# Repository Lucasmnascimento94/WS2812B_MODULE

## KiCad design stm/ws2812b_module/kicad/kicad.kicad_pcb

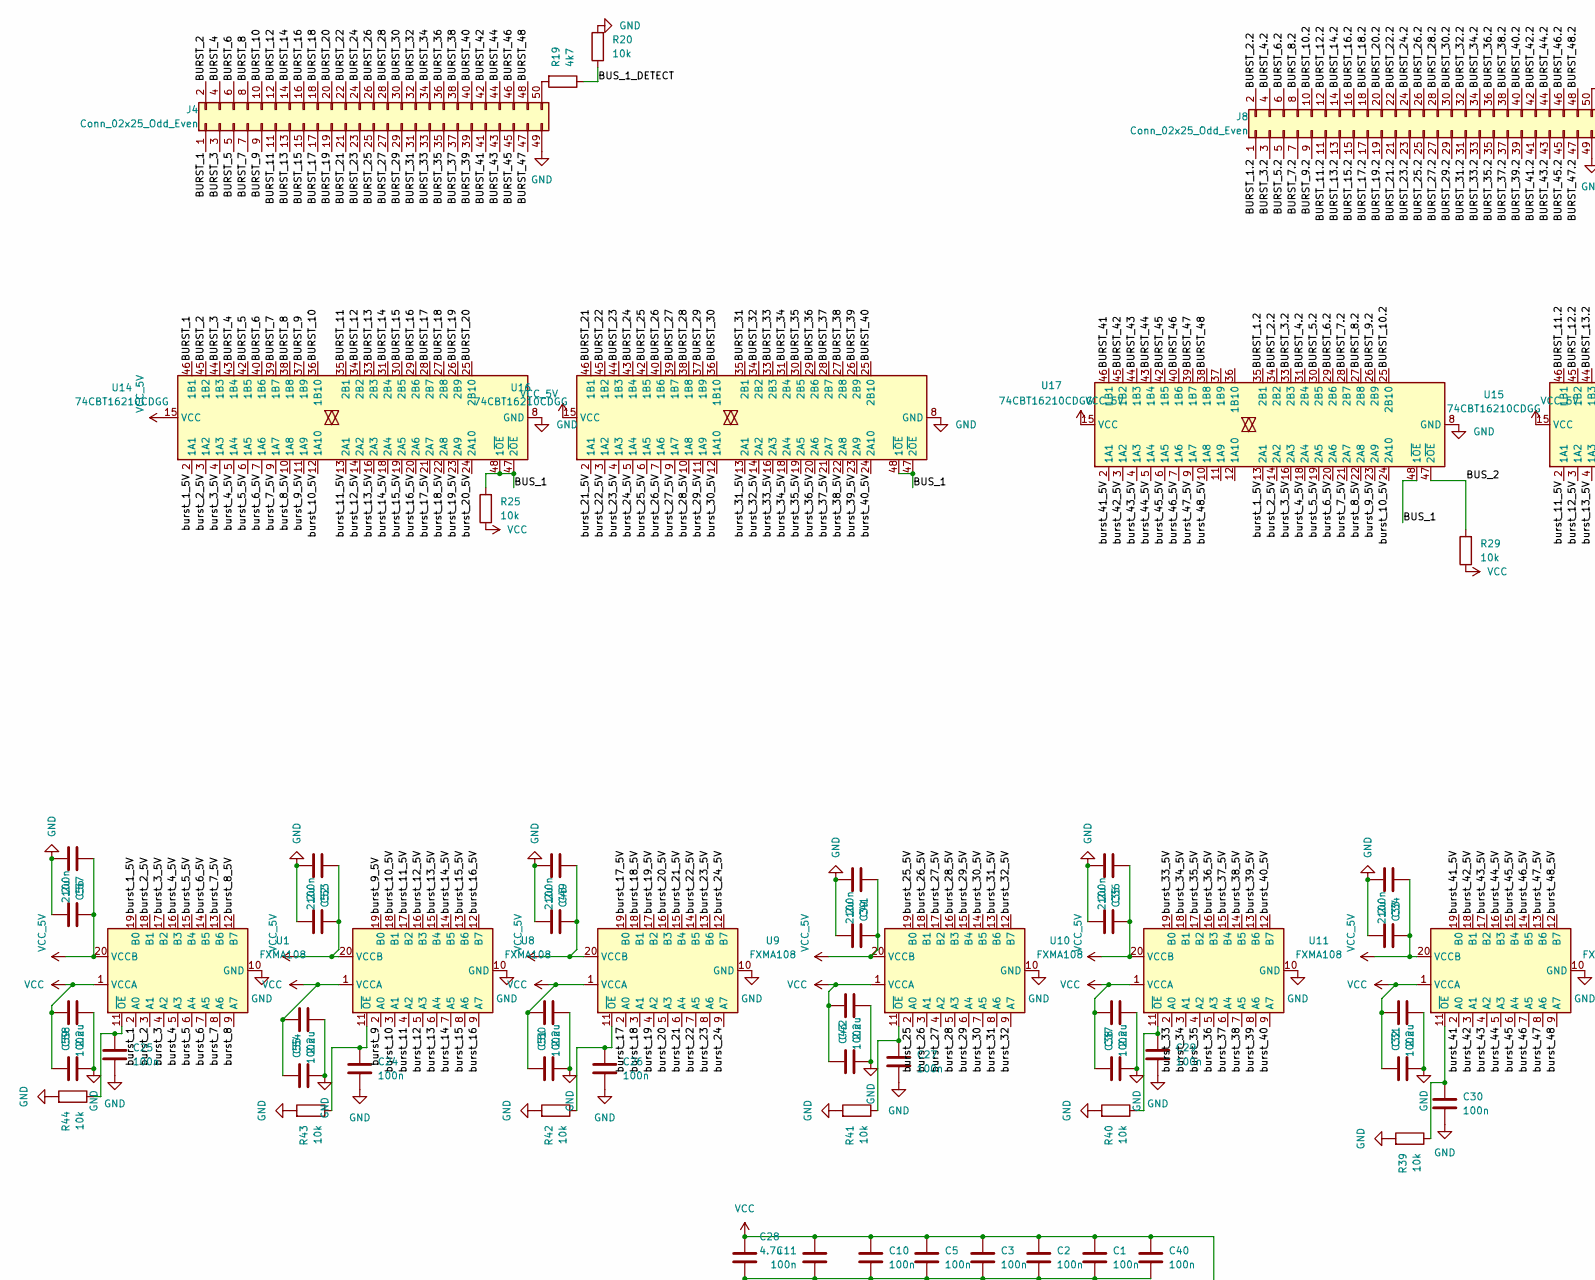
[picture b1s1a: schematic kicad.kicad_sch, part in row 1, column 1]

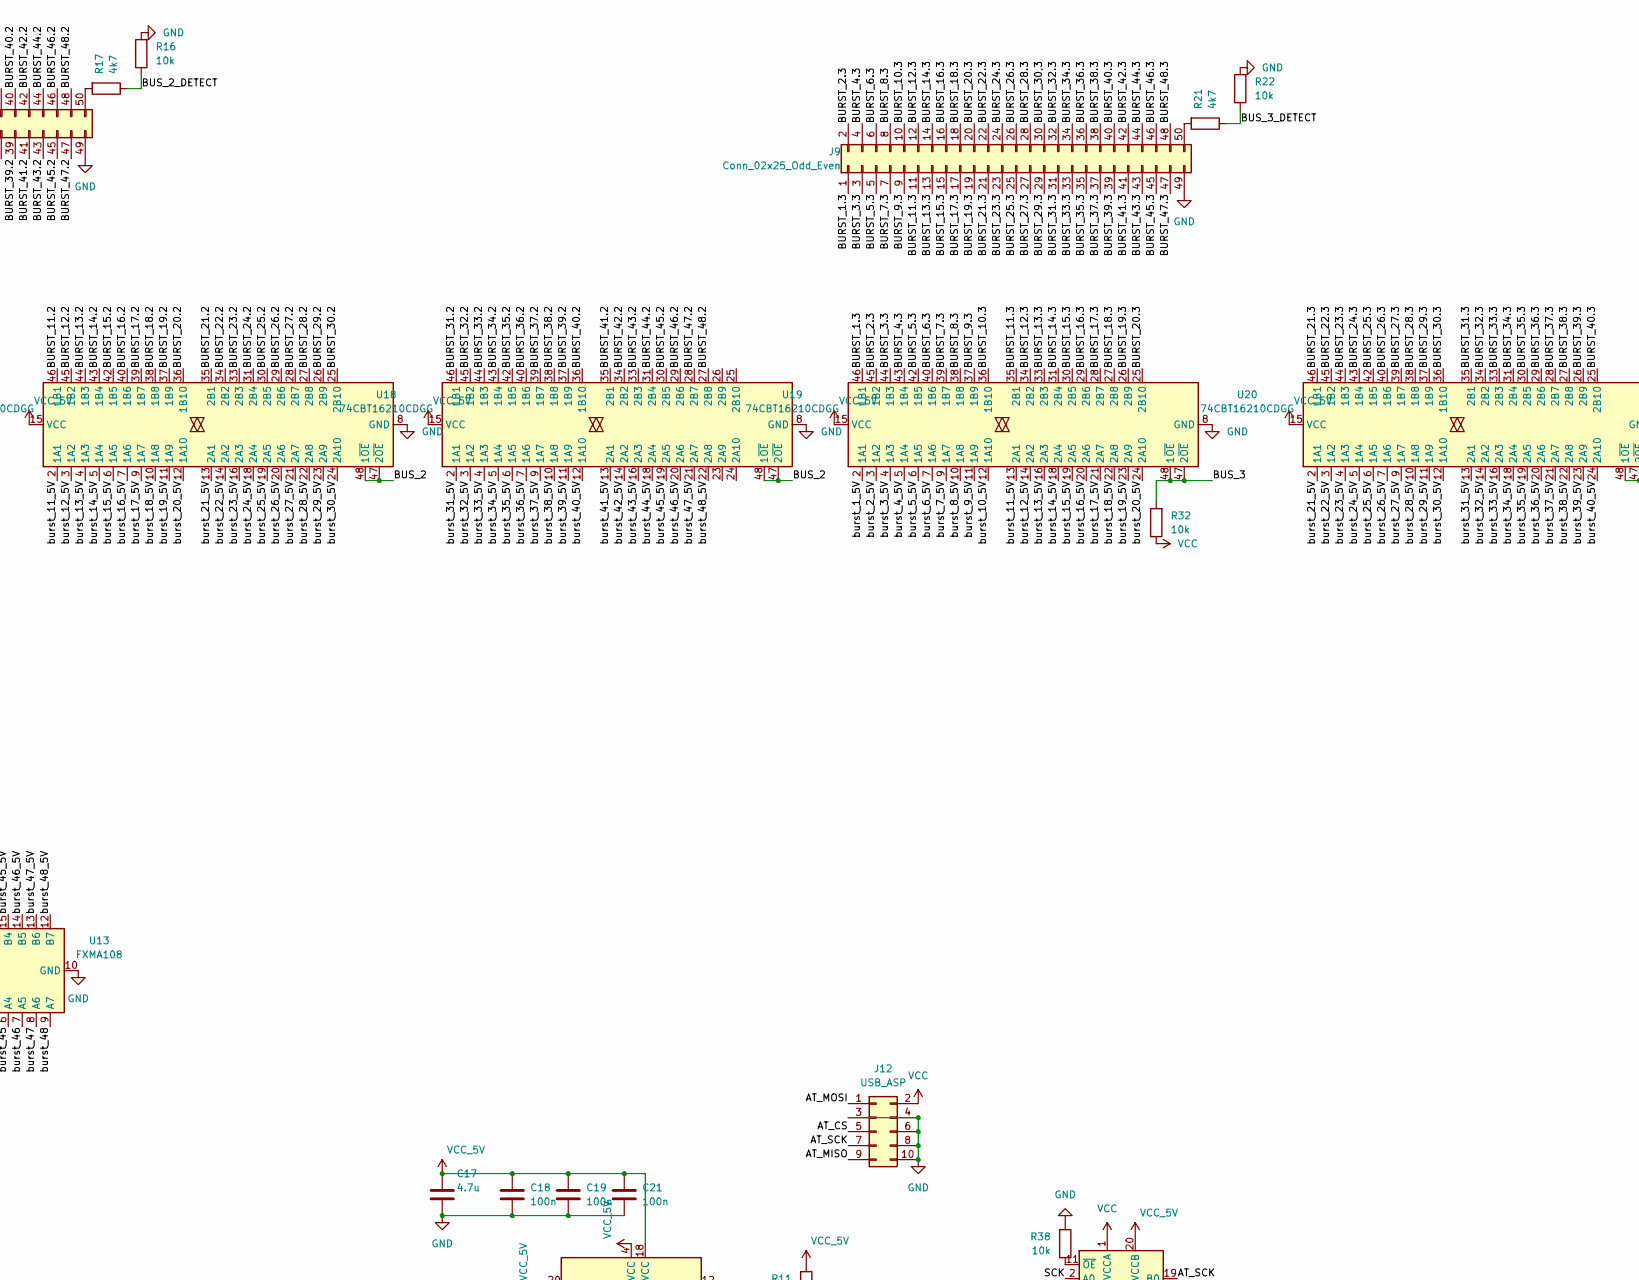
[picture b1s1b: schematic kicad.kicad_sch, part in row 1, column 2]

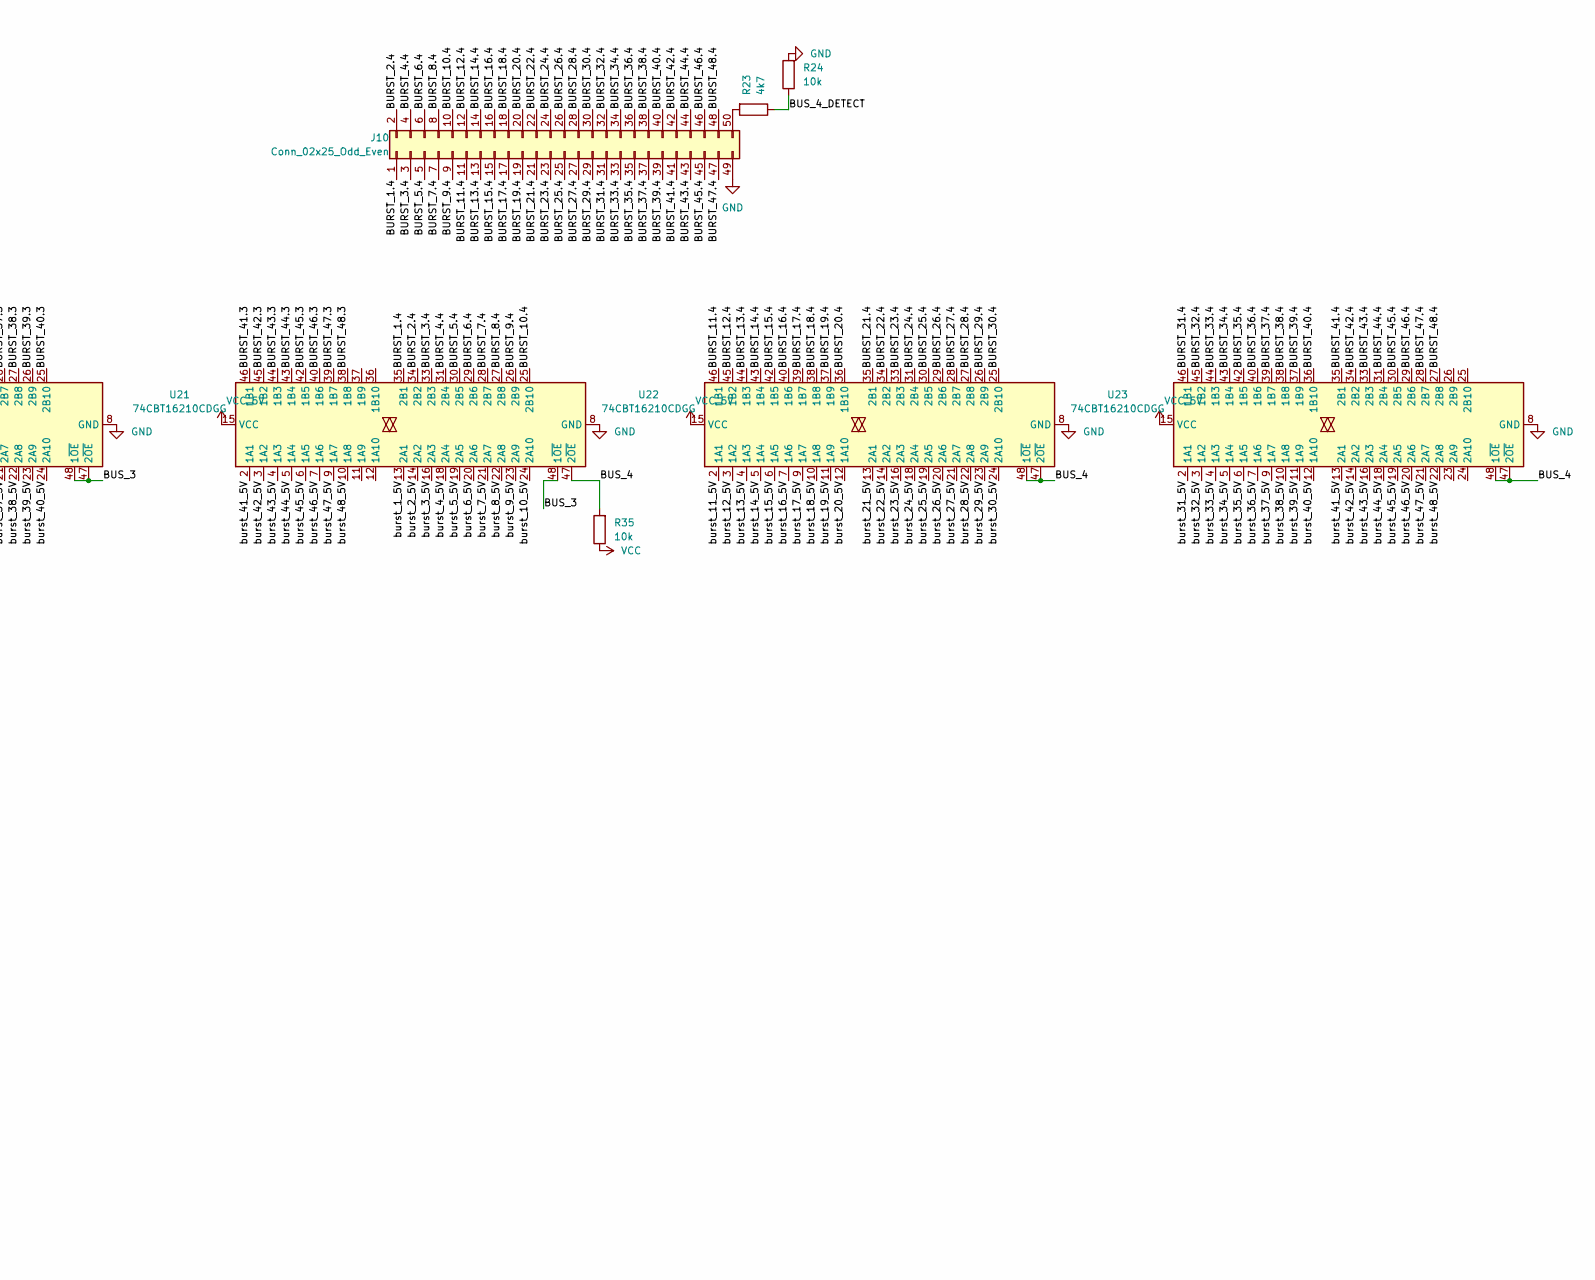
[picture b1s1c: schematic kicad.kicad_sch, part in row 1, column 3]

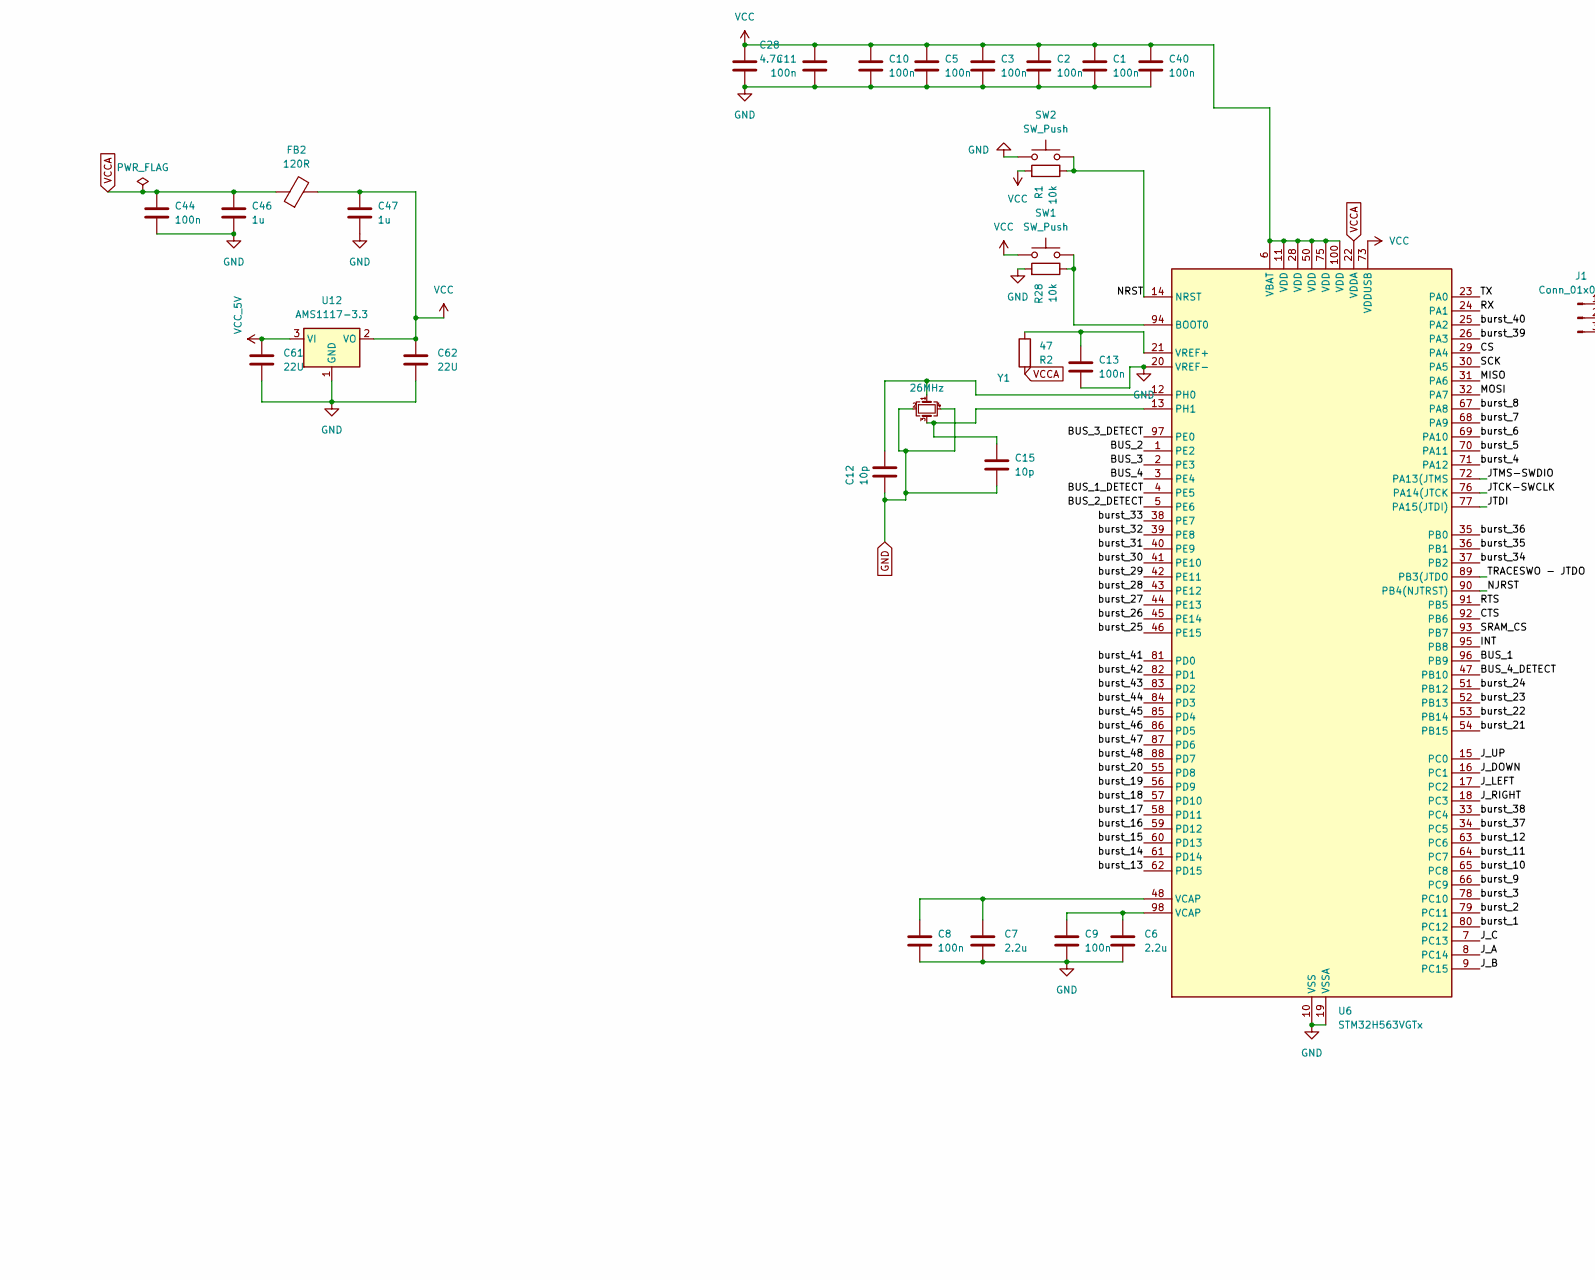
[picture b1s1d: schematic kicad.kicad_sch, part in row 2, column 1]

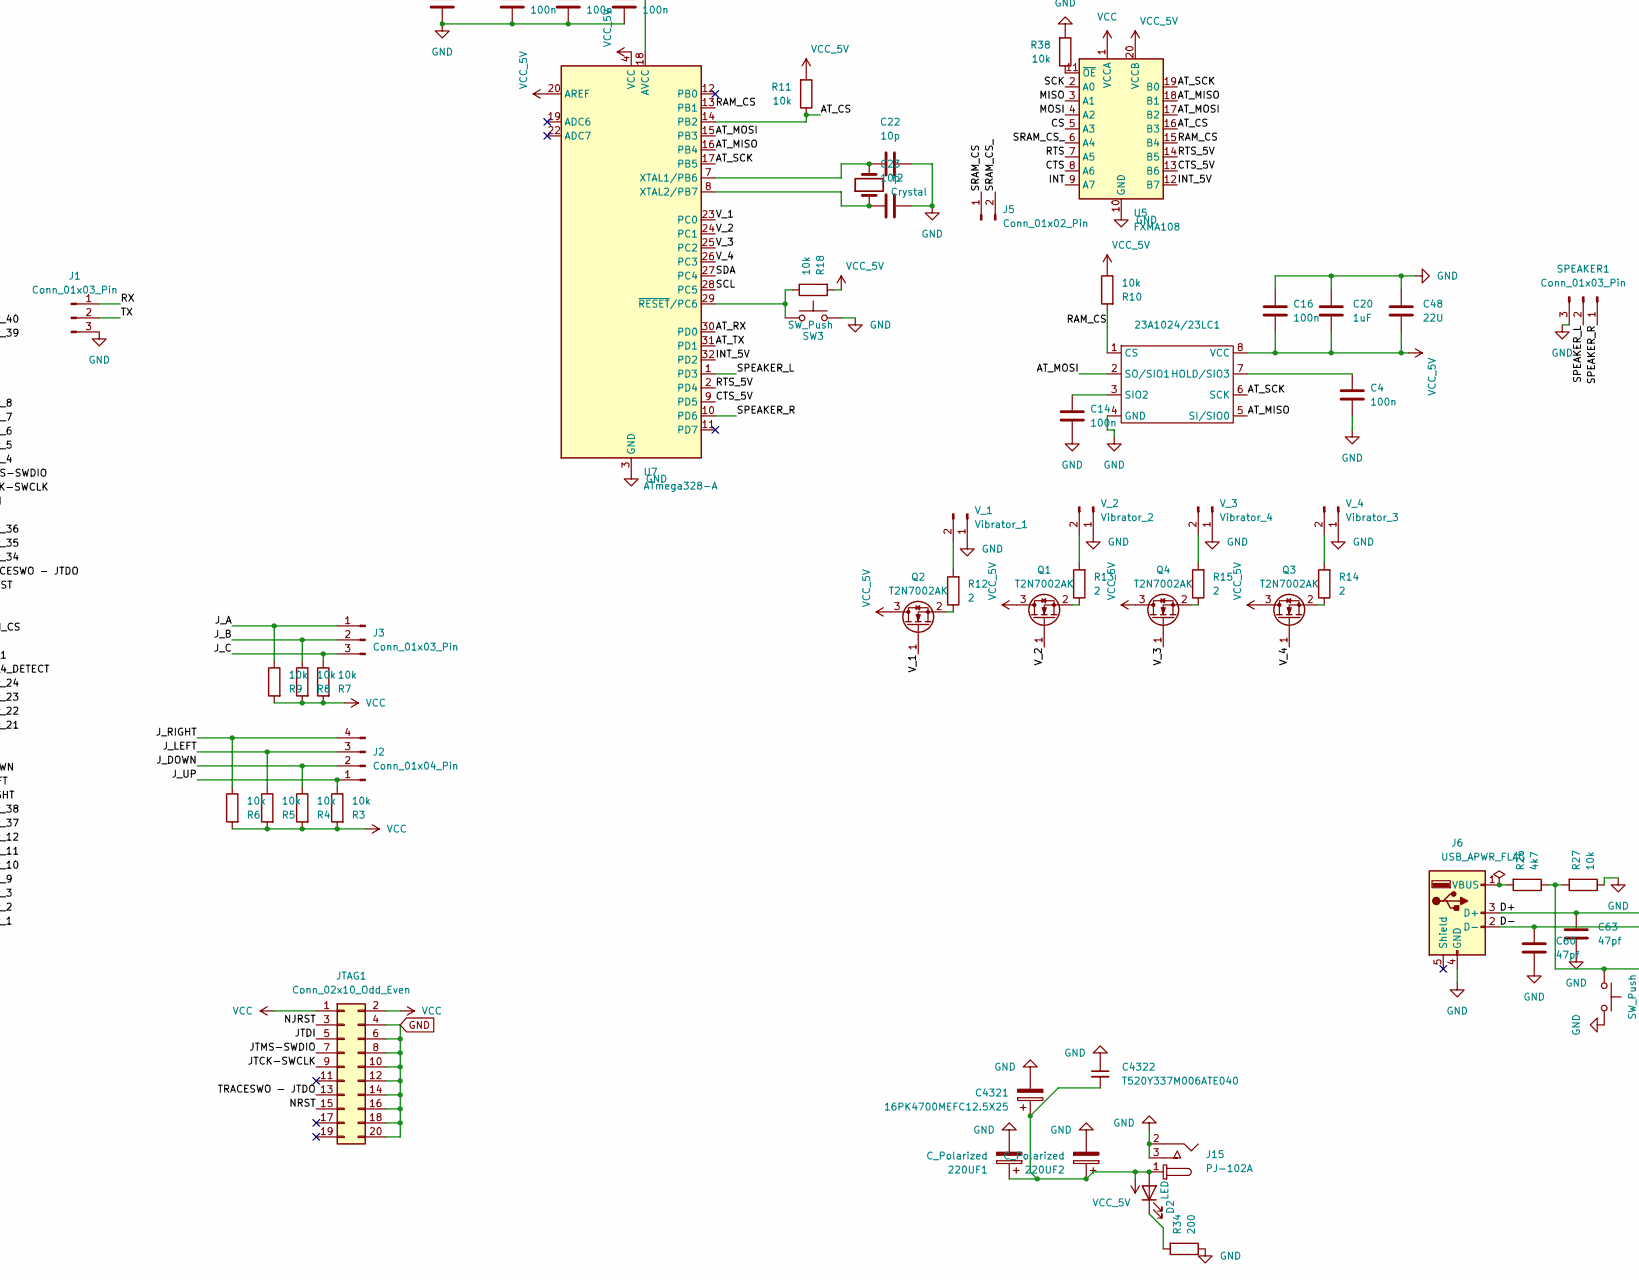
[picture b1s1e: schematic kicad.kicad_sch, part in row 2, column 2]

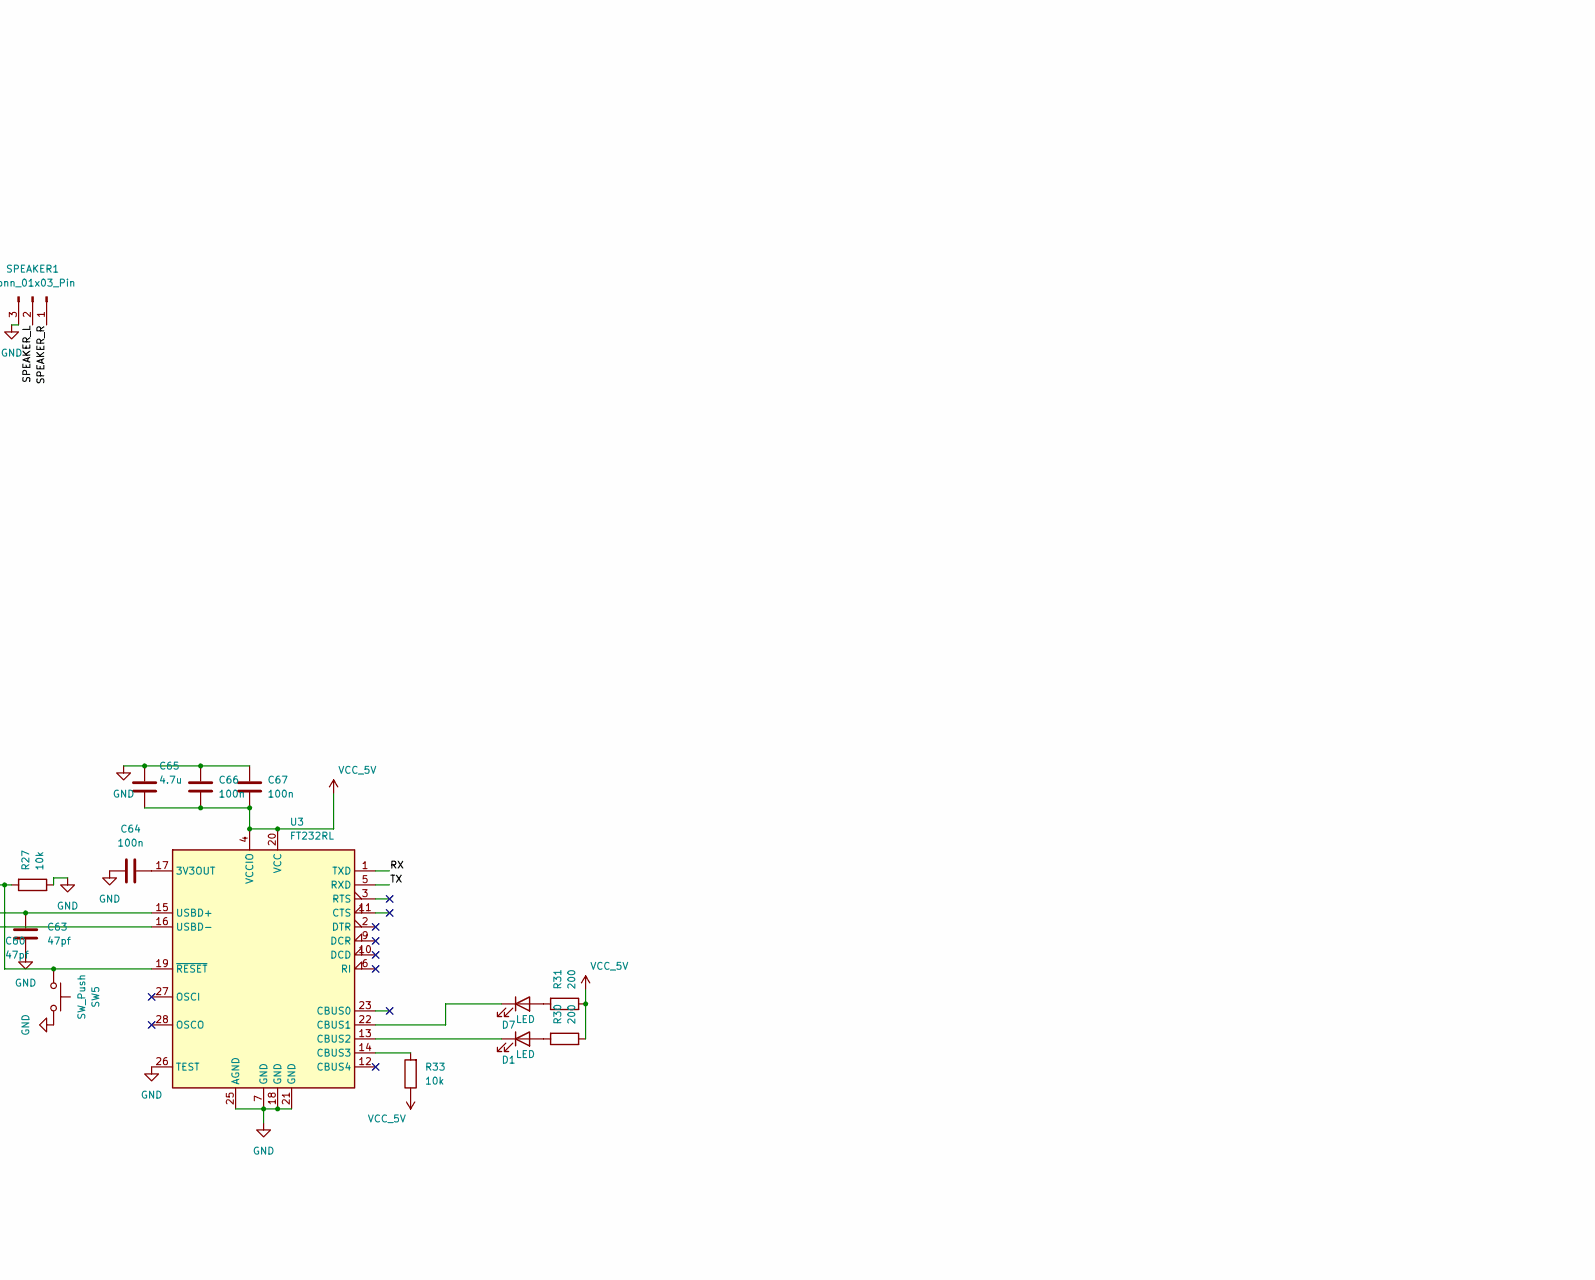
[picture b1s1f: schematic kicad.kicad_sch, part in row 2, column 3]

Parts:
23A1024/23LC1: CERDIP-8_W7.62mm_SideBrazed_Socket
220UF1, 220UF2: C_Polarized; C_Disc_D3.0mm_W1.6mm_P2.50mm
C1, C2, C3, C4, C5, C8, C9, C10, C11, C13, C14, C16, C18, C19, C21, C24, C25, C26, C27, C29, C30, C32, C34, C36, C38, C40, C41, C43, C44, C49, C51, C53, C55, C57, C59, C64, C66, C67: 100n; C_0402_1005Metric
C6, C7, C31, C33, C35, C37, C39, C42, C45, C50, C52, C54, C56, C58: 2.2u; C_0402_1005Metric
C12, C15, C22, C23: 10p; C_0402_1005Metric
C17, C28, C65: 4.7u; C_0603_1608Metric
C20: 1uF; C_0603_1608Metric
C46, C47: 1u; C_0603_1608Metric
C48, C61, C62: 22U; C_0805_2012Metric
C60, C63: 47pf; C_0402_1005Metric
C4321: 16PK4700MEFC12.5X25; CP_Radial_D5.0mm_P2.50mm
C4322: T520Y337M006ATE040; CP_Elec_10x10
D1, D2, D7: LED; LED_0603_1608Metric
FB2: 120R; L_0603_1608Metric
J1, J3: Conn_01x03_Pin; JST_EH_B3B-EH-A_1x03_P2.50mm_Vertical
J2: Conn_01x04_Pin; JST_EH_B4B-EH-A_1x04_P2.50mm_Vertical
J4, J8, J9, J10: Conn_02x25_Odd_Even; IDC-Header_2x25_P2.54mm_Vertical_SMD
J5: Conn_01x02_Pin; PinSocket_1x02_P2.54mm_Vertical
J6: USB_A; USB_B_Lumberg_2411_02_Horizontal
J12: USB_ASP; IDC-Header_2x05_P2.54mm_Vertical
J15: PJ-102A; BarrelJack_Horizontal; MPN PJ-102A; Digi-Key_PN CP-102A-ND
JTAG1: Conn_02x10_Odd_Even; IDC-Header_2x10_P2.54mm_Vertical
Q1, Q2, Q3, Q4: T2N7002AK; SOT-23
R1, R3, R4, R5, R6, R7, R8, R9, R10, R11, R16, R18, R20, R22, R24, R25, R27, R28, R29, R32, R33, R35, R38, R39, R40, R41, R42, R43, R44: 10k; R_0402_1005Metric
R2: 47; R_0402_1005Metric
R12, R13, R14, R15: 2; R_0402_1005Metric
R17, R19, R21, R23, R26: 4k7; R_0402_1005Metric
R30, R31, R34: 200; R_0402_1005Metric
SPEAKER1: Conn_01x03_Pin; JST_EH_B3B-EH-A_1x03_P2.50mm_Vertical
SW1, SW2, SW3, SW5: SW_Push; SW_PUSH_1P1T_6x3.5mm_H4.3_APEM_MJTP1243
U1, U5, U8, U9, U10, U11, U13: FXMA108; WQFN-20-1EP_2.5x4.5mm_P0.5mm_EP1x2.9mm
U3: FT232RL; SSOP-28_5.3x10.2mm_P0.65mm
U6: STM32H563VGTx; LQFP-100_14x14mm_P0.5mm
U7: ATmega328-A; TQFP-32_7x7mm_P0.8mm
U12: AMS1117-3.3; SOT-223-3_TabPin2
U14, U15, U16, U17, U18, U19, U20, U21, U22, U23: 74CBT16210CDGG; TSSOP-48_6.1x12.5mm_P0.5mm
V_1: Vibrator_1; JST_EH_B2B-EH-A_1x02_P2.50mm_Vertical
V_2: Vibrator_2; JST_EH_B2B-EH-A_1x02_P2.50mm_Vertical
V_3: Vibrator_4; JST_EH_B2B-EH-A_1x02_P2.50mm_Vertical
V_4: Vibrator_3; JST_EH_B2B-EH-A_1x02_P2.50mm_Vertical
Y1: 26MHz; Crystal_SMD_3225-4Pin_3.2x2.5mm_HandSoldering
Y2: Crystal; Resonator-2Pin_W6.0mm_H3.0mm

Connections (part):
/AT_CS: J12.5, R11.1, U5.16 (B3), U7.14 (PB2); also elsewhere on the board
/AT_RX: U7.30 (PD0); also elsewhere on the board
/AT_SCK: 23A1024/23LC1.6 (SCK), J12.7, U5.19 (B0), U7.17 (PB5); also elsewhere on the board
/AT_TX: U7.31 (PD1); also elsewhere on the board
/BURST_1: J4.1, U14.46 (1B1); also elsewhere on the board
/BURST_1.2: J8.1, U17.35 (2B1); also elsewhere on the board
/BURST_1.3: J9.1, U19.46 (1B1); also elsewhere on the board
/BURST_1.4: J10.1, U21.35 (2B1); also elsewhere on the board
/BURST_2: J4.2, U14.45 (1B2); also elsewhere on the board
/BURST_2.2: J8.2, U17.34 (2B2); also elsewhere on the board
/BURST_2.3: J9.2, U19.45 (1B2); also elsewhere on the board
/BURST_2.4: J10.2, U21.34 (2B2); also elsewhere on the board
/BURST_3: J4.3, U14.44 (1B3); also elsewhere on the board
/BURST_3.2: J8.3, U17.33 (2B3); also elsewhere on the board
/BURST_3.3: J9.3, U19.44 (1B3); also elsewhere on the board
/BURST_3.4: J10.3, U21.33 (2B3); also elsewhere on the board
/BURST_4: J4.4, U14.43 (1B4); also elsewhere on the board
/BURST_4.2: J8.4, U17.31 (2B4); also elsewhere on the board
/BURST_4.3: J9.4, U19.43 (1B4); also elsewhere on the board
/BURST_4.4: J10.4, U21.31 (2B4); also elsewhere on the board
/BURST_5: J4.5, U14.42 (1B5); also elsewhere on the board
/BURST_5.2: J8.5, U17.30 (2B5); also elsewhere on the board
/BURST_5.3: J9.5, U19.42 (1B5); also elsewhere on the board
/BURST_5.4: J10.5, U21.30 (2B5); also elsewhere on the board
/BURST_6: J4.6, U14.40 (1B6); also elsewhere on the board
/BURST_6.2: J8.6, U17.29 (2B6); also elsewhere on the board
/BURST_6.3: J9.6, U19.40 (1B6); also elsewhere on the board
/BURST_6.4: J10.6, U21.29 (2B6); also elsewhere on the board
/BURST_7: J4.7, U14.39 (1B7); also elsewhere on the board
/BURST_7.2: J8.7, U17.28 (2B7); also elsewhere on the board
/BURST_7.3: J9.7, U19.39 (1B7); also elsewhere on the board
/BURST_7.4: J10.7, U21.28 (2B7); also elsewhere on the board
/BURST_8: J4.8, U14.38 (1B8); also elsewhere on the board
/BURST_8.2: J8.8, U17.27 (2B8); also elsewhere on the board
/BURST_8.3: J9.8, U19.38 (1B8); also elsewhere on the board
/BURST_8.4: J10.8, U21.27 (2B8); also elsewhere on the board
/BURST_9: J4.9, U14.37 (1B9); also elsewhere on the board
/BURST_9.2: J8.9, U17.26 (2B9); also elsewhere on the board
/BURST_9.3: J9.9, U19.37 (1B9); also elsewhere on the board
/BURST_9.4: J10.9, U21.26 (2B9); also elsewhere on the board
/BURST_10: J4.10, U14.36 (1B10); also elsewhere on the board
/BURST_10.2: J8.10, U17.25 (2B10); also elsewhere on the board
/BURST_10.3: J9.10, U19.36 (1B10); also elsewhere on the board
/BURST_10.4: J10.10, U21.25 (2B10); also elsewhere on the board
/BURST_11: J4.11, U14.35 (2B1); also elsewhere on the board
/BURST_11.2: J8.11, U15.46 (1B1); also elsewhere on the board
/BURST_11.3: J9.11, U19.35 (2B1); also elsewhere on the board
/BURST_11.4: J10.11, U22.46 (1B1); also elsewhere on the board
/BURST_12: J4.12, U14.34 (2B2); also elsewhere on the board
/BURST_12.2: J8.12, U15.45 (1B2); also elsewhere on the board
/BURST_12.3: J9.12, U19.34 (2B2); also elsewhere on the board
/BURST_12.4: J10.12, U22.45 (1B2); also elsewhere on the board
/BURST_13: J4.13, U14.33 (2B3); also elsewhere on the board
/BURST_13.2: J8.13, U15.44 (1B3); also elsewhere on the board
/BURST_13.3: J9.13, U19.33 (2B3); also elsewhere on the board
/BURST_13.4: J10.13, U22.44 (1B3); also elsewhere on the board
/BURST_14: J4.14, U14.31 (2B4); also elsewhere on the board
/BURST_14.2: J8.14, U15.43 (1B4); also elsewhere on the board
/BURST_14.3: J9.14, U19.31 (2B4); also elsewhere on the board
/BURST_14.4: J10.14, U22.43 (1B4); also elsewhere on the board
/BURST_15: J4.15, U14.30 (2B5); also elsewhere on the board
/BURST_15.2: J8.15, U15.42 (1B5); also elsewhere on the board
/BURST_15.3: J9.15, U19.30 (2B5); also elsewhere on the board
/BURST_15.4: J10.15, U22.42 (1B5); also elsewhere on the board
/BURST_16: J4.16, U14.29 (2B6); also elsewhere on the board
/BURST_16.2: J8.16, U15.40 (1B6); also elsewhere on the board
/BURST_16.3: J9.16, U19.29 (2B6); also elsewhere on the board
/BURST_16.4: J10.16, U22.40 (1B6); also elsewhere on the board
/BURST_17: J4.17, U14.28 (2B7); also elsewhere on the board
/BURST_17.2: J8.17, U15.39 (1B7); also elsewhere on the board
/BURST_17.3: J9.17, U19.28 (2B7); also elsewhere on the board
/BURST_17.4: J10.17, U22.39 (1B7); also elsewhere on the board
/BURST_18: J4.18, U14.27 (2B8); also elsewhere on the board
/BURST_18.2: J8.18, U15.38 (1B8); also elsewhere on the board
/BURST_18.3: J9.18, U19.27 (2B8); also elsewhere on the board
/BURST_18.4: J10.18, U22.38 (1B8); also elsewhere on the board
/BURST_19: J4.19, U14.26 (2B9); also elsewhere on the board
/BURST_19.2: J8.19, U15.37 (1B9); also elsewhere on the board
/BURST_19.3: J9.19, U19.26 (2B9); also elsewhere on the board
/BURST_19.4: J10.19, U22.37 (1B9); also elsewhere on the board
/BURST_20: J4.20, U14.25 (2B10); also elsewhere on the board
/BURST_20.2: J8.20, U15.36 (1B10); also elsewhere on the board
/BURST_20.3: J9.20, U19.25 (2B10); also elsewhere on the board
/BURST_20.4: J10.20, U22.36 (1B10); also elsewhere on the board
/BURST_21: J4.21, U16.46 (1B1); also elsewhere on the board
/BURST_21.2: J8.21, U15.35 (2B1); also elsewhere on the board
/BURST_21.3: J9.21, U20.46 (1B1); also elsewhere on the board
/BURST_21.4: J10.21, U22.35 (2B1); also elsewhere on the board
/BURST_22: J4.22, U16.45 (1B2); also elsewhere on the board
/BURST_22.2: J8.22, U15.34 (2B2); also elsewhere on the board
/BURST_22.3: J9.22, U20.45 (1B2); also elsewhere on the board
/BURST_22.4: J10.22, U22.34 (2B2); also elsewhere on the board
/BURST_23: J4.23, U16.44 (1B3); also elsewhere on the board
/BURST_23.2: J8.23, U15.33 (2B3); also elsewhere on the board
/BURST_23.3: J9.23, U20.44 (1B3); also elsewhere on the board
/BURST_23.4: J10.23, U22.33 (2B3); also elsewhere on the board
/BURST_24: J4.24, U16.43 (1B4); also elsewhere on the board
/BURST_24.2: J8.24, U15.31 (2B4); also elsewhere on the board
/BURST_24.3: J9.24, U20.43 (1B4); also elsewhere on the board
/BURST_24.4: J10.24, U22.31 (2B4); also elsewhere on the board
/BURST_25: J4.25, U16.42 (1B5); also elsewhere on the board
/BURST_25.2: J8.25, U15.30 (2B5); also elsewhere on the board
/BURST_25.3: J9.25, U20.42 (1B5); also elsewhere on the board
/BURST_25.4: J10.25, U22.30 (2B5); also elsewhere on the board
/BURST_26: J4.26, U16.40 (1B6); also elsewhere on the board
/BURST_26.2: J8.26, U15.29 (2B6); also elsewhere on the board
/BURST_26.3: J9.26, U20.40 (1B6); also elsewhere on the board
/BURST_26.4: J10.26, U22.29 (2B6); also elsewhere on the board
/BURST_27: J4.27, U16.39 (1B7); also elsewhere on the board
/BURST_27.2: J8.27, U15.28 (2B7); also elsewhere on the board
/BURST_27.3: J9.27, U20.39 (1B7); also elsewhere on the board
/BURST_27.4: J10.27, U22.28 (2B7); also elsewhere on the board
/BURST_28: J4.28, U16.38 (1B8); also elsewhere on the board
/BURST_28.2: J8.28, U15.27 (2B8); also elsewhere on the board
/BURST_28.3: J9.28, U20.38 (1B8); also elsewhere on the board
/BURST_28.4: J10.28, U22.27 (2B8); also elsewhere on the board
/BURST_29: J4.29, U16.37 (1B9); also elsewhere on the board
/BURST_29.2: J8.29, U15.26 (2B9); also elsewhere on the board
/BURST_29.3: J9.29, U20.37 (1B9); also elsewhere on the board
/BURST_29.4: J10.29, U22.26 (2B9); also elsewhere on the board
/BURST_30: J4.30, U16.36 (1B10); also elsewhere on the board
/BURST_30.2: J8.30, U15.25 (2B10); also elsewhere on the board
/BURST_30.3: U20.36 (1B10); also elsewhere on the board
/BURST_30.4: J10.30, U22.25 (2B10); also elsewhere on the board
/BURST_31: J4.31, U16.35 (2B1); also elsewhere on the board
/BURST_31.2: J8.31, U18.46 (1B1); also elsewhere on the board
/BURST_31.3: J9.31, U20.35 (2B1); also elsewhere on the board
/BURST_31.4: J10.31, U23.46 (1B1); also elsewhere on the board
/BURST_32: J4.32, U16.34 (2B2); also elsewhere on the board
/BURST_32.2: J8.32, U18.45 (1B2); also elsewhere on the board
/BURST_32.3: J9.32, U20.34 (2B2); also elsewhere on the board
/BURST_32.4: J10.32, U23.45 (1B2); also elsewhere on the board
/BURST_33: J4.33, U16.33 (2B3); also elsewhere on the board
/BURST_33.2: J8.33, U18.44 (1B3); also elsewhere on the board
/BURST_33.3: J9.33, U20.33 (2B3); also elsewhere on the board
/BURST_33.4: J10.33, U23.44 (1B3); also elsewhere on the board
/BURST_34: J4.34, U16.31 (2B4); also elsewhere on the board
/BURST_34.2: J8.34, U18.43 (1B4); also elsewhere on the board
/BURST_34.3: J9.34, U20.31 (2B4); also elsewhere on the board
/BURST_34.4: J10.34, U23.43 (1B4); also elsewhere on the board
/BURST_35: J4.35, U16.30 (2B5); also elsewhere on the board
/BURST_35.2: J8.35, U18.42 (1B5); also elsewhere on the board
/BURST_35.3: J9.35, U20.30 (2B5); also elsewhere on the board
/BURST_35.4: J10.35, U23.42 (1B5); also elsewhere on the board
/BURST_36: J4.36, U16.29 (2B6); also elsewhere on the board
/BURST_36.2: J8.36, U18.40 (1B6); also elsewhere on the board
/BURST_36.3: J9.36, U20.29 (2B6); also elsewhere on the board
/BURST_36.4: J10.36, U23.40 (1B6); also elsewhere on the board
/BURST_37: J4.37, U16.28 (2B7); also elsewhere on the board
/BURST_37.2: J8.37, U18.39 (1B7); also elsewhere on the board
/BURST_37.3: J9.37, U20.28 (2B7); also elsewhere on the board
/BURST_37.4: J10.37, U23.39 (1B7); also elsewhere on the board
/BURST_38: J4.38, U16.27 (2B8); also elsewhere on the board
/BURST_38.2: J8.38, U18.38 (1B8); also elsewhere on the board
/BURST_38.3: J9.38, U20.27 (2B8); also elsewhere on the board
/BURST_38.4: J10.38, U23.38 (1B8); also elsewhere on the board
/BURST_39: J4.39, U16.26 (2B9); also elsewhere on the board
/BURST_39.2: J8.39, U18.37 (1B9); also elsewhere on the board
/BURST_39.3: J9.39, U20.26 (2B9); also elsewhere on the board
/BURST_39.4: J10.39, U23.37 (1B9); also elsewhere on the board
/BURST_40: J4.40, U16.25 (2B10); also elsewhere on the board
/BURST_40.2: J8.40, U18.36 (1B10); also elsewhere on the board
/BURST_40.3: J9.40, U20.25 (2B10); also elsewhere on the board
/BURST_40.4: J10.40, U23.36 (1B10); also elsewhere on the board
/BURST_41: J4.41, U17.46 (1B1); also elsewhere on the board
/BURST_41.2: J8.41, U18.35 (2B1); also elsewhere on the board
/BURST_41.3: J9.41, U21.46 (1B1); also elsewhere on the board
/BURST_41.4: J10.41, U23.35 (2B1); also elsewhere on the board
/BURST_42: J4.42, U17.45 (1B2); also elsewhere on the board
/BURST_42.2: J8.42, U18.34 (2B2); also elsewhere on the board
/BURST_42.3: J9.42, U21.45 (1B2); also elsewhere on the board
/BURST_42.4: J10.42, U23.34 (2B2); also elsewhere on the board
/BURST_43: J4.43, U17.44 (1B3); also elsewhere on the board
/BURST_43.2: J8.43, U18.33 (2B3); also elsewhere on the board
/BURST_43.3: J9.43, U21.44 (1B3); also elsewhere on the board
/BURST_43.4: J10.43, U23.33 (2B3); also elsewhere on the board
/BURST_44: J4.44, U17.43 (1B4); also elsewhere on the board
/BURST_44.2: J8.44, U18.31 (2B4); also elsewhere on the board
/BURST_44.3: J9.44, U21.43 (1B4); also elsewhere on the board
/BURST_44.4: J10.44, U23.31 (2B4); also elsewhere on the board
/BURST_45: J4.45, U17.42 (1B5); also elsewhere on the board
/BURST_45.2: J8.45, U18.30 (2B5); also elsewhere on the board
/BURST_45.3: J9.45, U21.42 (1B5); also elsewhere on the board
/BURST_45.4: J10.45, U23.30 (2B5); also elsewhere on the board
/BURST_46: J4.46, U17.40 (1B6); also elsewhere on the board
/BURST_46.2: J8.46, U18.29 (2B6); also elsewhere on the board
/BURST_46.3: J9.46, U21.40 (1B6); also elsewhere on the board
/BURST_46.4: J10.46, U23.29 (2B6); also elsewhere on the board
/BURST_47: J4.47, U17.39 (1B7); also elsewhere on the board
/BURST_47.2: J8.47, U18.28 (2B7); also elsewhere on the board
/BURST_47.3: J9.47, U21.39 (1B7); also elsewhere on the board
/BURST_47.4: J10.47, U23.28 (2B7); also elsewhere on the board
/BURST_48: J4.48, U17.38 (1B8); also elsewhere on the board
/BURST_48.2: J8.48, U18.27 (2B8); also elsewhere on the board
/BURST_48.3: J9.48, U21.38 (1B8); also elsewhere on the board
/BURST_48.4: J10.48, U23.27 (2B8); also elsewhere on the board
/BUS_1: R25.2, U6.96 (PB9), U14.47 (2~OE), U14.48 (1~OE), U16.47 (2~OE), U16.48 (1~OE), U17.48 (1~OE)
/BUS_1_DETECT: R19.1, R20.1, U6.4 (PE5)
/BUS_2: R29.2, U6.1 (PE2), U15.47 (2~OE), U15.48 (1~OE), U17.47 (2~OE), U18.47 (2~OE), U18.48 (1~OE)
/BUS_2_DETECT: R16.1, R17.1, U6.5 (PE6)
/BUS_3: R32.2, U6.2 (PE3), U19.47 (2~OE), U19.48 (1~OE), U20.47 (2~OE), U20.48 (1~OE), U21.48 (1~OE)
/BUS_3_DETECT: R21.1, R22.1, U6.97 (PE0)
/BUS_4: R35.2, U6.3 (PE4), U21.47 (2~OE), U22.47 (2~OE), U22.48 (1~OE), U23.47 (2~OE), U23.48 (1~OE)
/BUS_4_DETECT: R23.1, R24.1, U6.47 (PB10)
/CS: U5.5 (A3), U6.29 (PA4)
/CTS: U5.8 (A6), U6.92 (PB6)
/CTS_5V: U5.13 (B6), U7.9 (PD5)
/D+: C63.1, J6.3 (D+), U3.15 (USBD+)
/D-: C60.1, J6.2 (D-), U3.16 (USBD-)
/INT: U5.9 (A7), U6.95 (PB8)
/INT_5V: U5.12 (B7), U7.32 (PD2)
/JTCK-SWCLK: JTAG1.9, U6.76 (PA14(JTCK)
/JTDI: JTAG1.5, U6.77 (PA15(JTDI))
/JTMS-SWDIO: JTAG1.7, U6.72 (PA13(JTMS)
/J_A: J3.1, R9.1, U6.8 (PC14)
/J_B: J3.2, R8.1, U6.9 (PC15)
/J_C: J3.3, R7.1, U6.7 (PC13)
/J_DOWN: J2.2, R4.1, U6.16 (PC1)
/J_LEFT: J2.3, R5.1, U6.17 (PC2)
/J_RIGHT: J2.4, R6.1, U6.18 (PC3)
/J_UP: J2.1, R3.1, U6.15 (PC0)
/MISO: U5.3 (A1), U6.31 (PA6)
/MOSI: U5.4 (A2), U6.32 (PA7)
/NJRST: JTAG1.3, U6.90 (PB4(NJTRST))
/NRST: JTAG1.15, R1.1, SW2.2, U6.14 (NRST); also elsewhere on the board
/RAM_CS: 23A1024/23LC1.1 (CS), R10.2, U5.15 (B4), U7.13 (PB1)
/RTS: U5.7 (A5), U6.91 (PB5)
/RTS_5V: U5.14 (B5), U7.2 (PD4)
/RX: J1.1, U3.1 (TXD), U6.24 (PA1); also elsewhere on the board
/SCK: U5.2 (A0), U6.30 (PA5)
/SCL: U7.28 (PC5); also elsewhere on the board
/SDA: U7.27 (PC4); also elsewhere on the board
/SPEAKER_L: SPEAKER1.2, U7.1 (PD3)
/SPEAKER_R: SPEAKER1.1, U7.10 (PD6)
/SRAM_CS: J5.1, U6.93 (PB7)
/SRAM_CS_: J5.2, U5.6 (A4)
/TRACESWO - JTDO: JTAG1.13, U6.89 (PB3(JTDO)
/TX: J1.2, U3.5 (RXD), U6.23 (PA0); also elsewhere on the board
/V_1: Q2.1 (G), U7.23 (PC0)
/V_2: Q1.1 (G), U7.24 (PC1)
/V_3: Q4.1 (G), U7.25 (PC2)
/V_4: Q3.1 (G), U7.26 (PC3)
/burst_1_: U1.2 (A0), U6.80 (PC12)
/burst_1_5V: U1.19 (B0), U14.2 (1A1), U17.13 (2A1), U19.2 (1A1), U21.13 (2A1)
/burst_2_: U1.3 (A1), U6.79 (PC11)
/burst_2_5V: U1.18 (B1), U14.3 (1A2), U17.14 (2A2), U19.3 (1A2), U21.14 (2A2)
/burst_3_: U1.4 (A2), U6.78 (PC10)
/burst_3_5V: U1.17 (B2), U14.4 (1A3), U17.16 (2A3), U19.4 (1A3), U21.16 (2A3)
/burst_4_: U1.5 (A3), U6.71 (PA12)
/burst_4_5V: U1.16 (B3), U14.5 (1A4), U17.18 (2A4), U19.5 (1A4), U21.18 (2A4)
/burst_5_: U1.6 (A4), U6.70 (PA11)
/burst_5_5V: U1.15 (B4), U14.6 (1A5), U17.19 (2A5), U19.6 (1A5), U21.19 (2A5)
/burst_6_: U1.7 (A5), U6.69 (PA10)
/burst_6_5V: U1.14 (B5), U14.7 (1A6), U17.20 (2A6), U19.7 (1A6), U21.20 (2A6)
/burst_7_: U1.8 (A6), U6.68 (PA9)
/burst_7_5V: U1.13 (B6), U14.9 (1A7), U17.21 (2A7), U19.9 (1A7), U21.21 (2A7)
/burst_8_: U1.9 (A7), U6.67 (PA8)
/burst_8_5V: U1.12 (B7), U14.10 (1A8), U17.22 (2A8), U19.10 (1A8), U21.22 (2A8)
/burst_9_: U6.66 (PC9), U8.2 (A0)
/burst_9_5V: U8.19 (B0), U14.11 (1A9), U17.23 (2A9), U19.11 (1A9), U21.23 (2A9)
/burst_10_: U6.65 (PC8), U8.3 (A1)
/burst_10_5V: U8.18 (B1), U14.12 (1A10), U17.24 (2A10), U19.12 (1A10), U21.24 (2A10)
/burst_11_: U6.64 (PC7), U8.4 (A2)
/burst_11_5V: U8.17 (B2), U14.13 (2A1), U15.2 (1A1), U19.13 (2A1), U22.2 (1A1)
/burst_12_: U6.63 (PC6), U8.5 (A3)
/burst_12_5V: U8.16 (B3), U14.14 (2A2), U15.3 (1A2), U19.14 (2A2), U22.3 (1A2)
/burst_13_: U6.62 (PD15), U8.6 (A4)
/burst_13_5V: U8.15 (B4), U14.16 (2A3), U15.4 (1A3), U19.16 (2A3), U22.4 (1A3)
/burst_14_: U6.61 (PD14), U8.7 (A5)
/burst_14_5V: U8.14 (B5), U14.18 (2A4), U15.5 (1A4), U19.18 (2A4), U22.5 (1A4)
/burst_15_: U6.60 (PD13), U8.8 (A6)
/burst_15_5V: U8.13 (B6), U14.19 (2A5), U15.6 (1A5), U19.19 (2A5), U22.6 (1A5)
/burst_16_: U6.59 (PD12), U8.9 (A7)
/burst_16_5V: U8.12 (B7), U14.20 (2A6), U15.7 (1A6), U19.20 (2A6), U22.7 (1A6)
/burst_17_: U6.58 (PD11), U9.2 (A0)
/burst_17_5V: U9.19 (B0), U14.21 (2A7), U15.9 (1A7), U19.21 (2A7), U22.9 (1A7)
/burst_18_: U6.57 (PD10), U9.3 (A1)
/burst_18_5V: U9.18 (B1), U14.22 (2A8), U15.10 (1A8), U19.22 (2A8), U22.10 (1A8)
/burst_19_: U6.56 (PD9), U9.4 (A2)
/burst_19_5V: U9.17 (B2), U14.23 (2A9), U15.11 (1A9), U19.23 (2A9), U22.11 (1A9)
/burst_20_: U6.55 (PD8), U9.5 (A3)
/burst_20_5V: U9.16 (B3), U14.24 (2A10), U15.12 (1A10), U19.24 (2A10), U22.12 (1A10)
/burst_21_: U6.54 (PB15), U9.6 (A4)
/burst_21_5V: U9.15 (B4), U15.13 (2A1), U16.2 (1A1), U20.2 (1A1), U22.13 (2A1)
/burst_22_: U6.53 (PB14), U9.7 (A5)
/burst_22_5V: U9.14 (B5), U15.14 (2A2), U16.3 (1A2), U20.3 (1A2), U22.14 (2A2)
/burst_23_: U6.52 (PB13), U9.8 (A6)
/burst_23_5V: U9.13 (B6), U15.16 (2A3), U16.4 (1A3), U20.4 (1A3), U22.16 (2A3)
/burst_24_: U6.51 (PB12), U9.9 (A7)
/burst_24_5V: U9.12 (B7), U15.18 (2A4), U16.5 (1A4), U20.5 (1A4), U22.18 (2A4)
/burst_25_: U6.46 (PE15), U10.2 (A0)
/burst_25_5V: U10.19 (B0), U15.19 (2A5), U16.6 (1A5), U20.6 (1A5), U22.19 (2A5)
/burst_26_: U6.45 (PE14), U10.3 (A1)
/burst_26_5V: U10.18 (B1), U15.20 (2A6), U16.7 (1A6), U20.7 (1A6), U22.20 (2A6)
/burst_27_: U6.44 (PE13), U10.4 (A2)
/burst_27_5V: U10.17 (B2), U15.21 (2A7), U16.9 (1A7), U20.9 (1A7), U22.21 (2A7)
/burst_28_: U6.43 (PE12), U10.5 (A3)
/burst_28_5V: U10.16 (B3), U15.22 (2A8), U16.10 (1A8), U20.10 (1A8), U22.22 (2A8)
/burst_29_: U6.42 (PE11), U10.6 (A4)
/burst_29_5V: U10.15 (B4), U15.23 (2A9), U16.11 (1A9), U20.11 (1A9), U22.23 (2A9)
/burst_30_: U6.41 (PE10), U10.7 (A5)
/burst_30_5V: U10.14 (B5), U15.24 (2A10), U16.12 (1A10), U20.12 (1A10), U22.24 (2A10)
/burst_31_: U6.40 (PE9), U10.8 (A6)
/burst_31_5V: U10.13 (B6), U16.13 (2A1), U18.2 (1A1), U20.13 (2A1), U23.2 (1A1)
/burst_32_: U6.39 (PE8), U10.9 (A7)
/burst_32_5V: U10.12 (B7), U16.14 (2A2), U18.3 (1A2), U20.14 (2A2), U23.3 (1A2)
/burst_33_: U6.38 (PE7), U11.2 (A0)
/burst_33_5V: U11.19 (B0), U16.16 (2A3), U18.4 (1A3), U20.16 (2A3), U23.4 (1A3)
/burst_34_: U6.37 (PB2), U11.3 (A1)
/burst_34_5V: U11.18 (B1), U16.18 (2A4), U18.5 (1A4), U20.18 (2A4), U23.5 (1A4)
/burst_35_: U6.36 (PB1), U11.4 (A2)
/burst_35_5V: U11.17 (B2), U16.19 (2A5), U18.6 (1A5), U20.19 (2A5), U23.6 (1A5)
/burst_36_: U6.35 (PB0), U11.5 (A3)
/burst_36_5V: U11.16 (B3), U16.20 (2A6), U18.7 (1A6), U20.20 (2A6), U23.7 (1A6)
/burst_37_: U6.34 (PC5), U11.6 (A4)
/burst_37_5V: U11.15 (B4), U16.21 (2A7), U18.9 (1A7), U20.21 (2A7), U23.9 (1A7)
/burst_38_: U6.33 (PC4), U11.7 (A5)
/burst_38_5V: U11.14 (B5), U16.22 (2A8), U18.10 (1A8), U20.22 (2A8), U23.10 (1A8)
/burst_39_: U6.26 (PA3), U11.8 (A6)
/burst_39_5V: U11.13 (B6), U16.23 (2A9), U18.11 (1A9), U20.23 (2A9), U23.11 (1A9)
/burst_40_: U6.25 (PA2), U11.9 (A7)
/burst_40_5V: U11.12 (B7), U16.24 (2A10), U18.12 (1A10), U20.24 (2A10), U23.12 (1A10)
/burst_41_: U6.81 (PD0), U13.2 (A0)
/burst_41_5V: U13.19 (B0), U17.2 (1A1), U18.13 (2A1), U21.2 (1A1), U23.13 (2A1)
/burst_42_: U6.82 (PD1), U13.3 (A1)
/burst_42_5V: U13.18 (B1), U17.3 (1A2), U18.14 (2A2), U21.3 (1A2), U23.14 (2A2)
/burst_43_: U6.83 (PD2), U13.4 (A2)
/burst_43_5V: U13.17 (B2), U17.4 (1A3), U18.16 (2A3), U21.4 (1A3), U23.16 (2A3)
/burst_44_: U6.84 (PD3), U13.5 (A3)
/burst_44_5V: U13.16 (B3), U17.5 (1A4), U18.18 (2A4), U21.5 (1A4), U23.18 (2A4)
/burst_45_: U6.85 (PD4), U13.6 (A4)
/burst_45_5V: U13.15 (B4), U17.6 (1A5), U18.19 (2A5), U21.6 (1A5), U23.19 (2A5)
/burst_46_: U6.86 (PD5), U13.7 (A5)
/burst_46_5V: U13.14 (B5), U17.7 (1A6), U18.20 (2A6), U21.7 (1A6), U23.20 (2A6)
/burst_47_: U6.87 (PD6), U13.8 (A6)
/burst_47_5V: U13.13 (B6), U17.9 (1A7), U18.21 (2A7), U21.9 (1A7), U23.21 (2A7)
/burst_48_: U6.88 (PD7), U13.9 (A7)
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
